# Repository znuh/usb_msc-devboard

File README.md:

# Devboard for USB mass storage

EDA: [KiCad7](https://www.kicad.org/)

## Parts
* MCU: [STM32F730R8Tx](https://www.st.com/en/microcontrollers-microprocessors/stm32f730r8.html) (or compatible)
* Mass storage: MicroSD via [DM3D-SF](https://www.hirose.com/product/series/DM3#) socket (attached to SDMMC1 of STM32)
* [USB3318](https://www.microchip.com/en-us/product/USB3318) USB high speed PHY
* 3.3V voltage regulator: [AP7313-33SR](https://www.diodes.com/part/view/AP7313/) or compatible
* PCB: 4 layer (Sig1, GND, 3.3V, Sig2) stackup
* 1x USB-C, 1x Micro USB
* 3x 0603 LEDs (power, user1, user2)
* 1x Button (Bootloader + user defined)
* passives: 0402 and 0603
* all componentes are on top, none on bottom

## Notes
* USB-C connector for hi-speed USB
* Micro USB connector for dev/debugging/DFU bootloader
* Testpads on bottom for UART (debugging, etc.)
* only one 13MHz crystal, connected to STM32 - MCO1 output of STM32 clocks USB PHY
* serial termination resistors in all clock lines

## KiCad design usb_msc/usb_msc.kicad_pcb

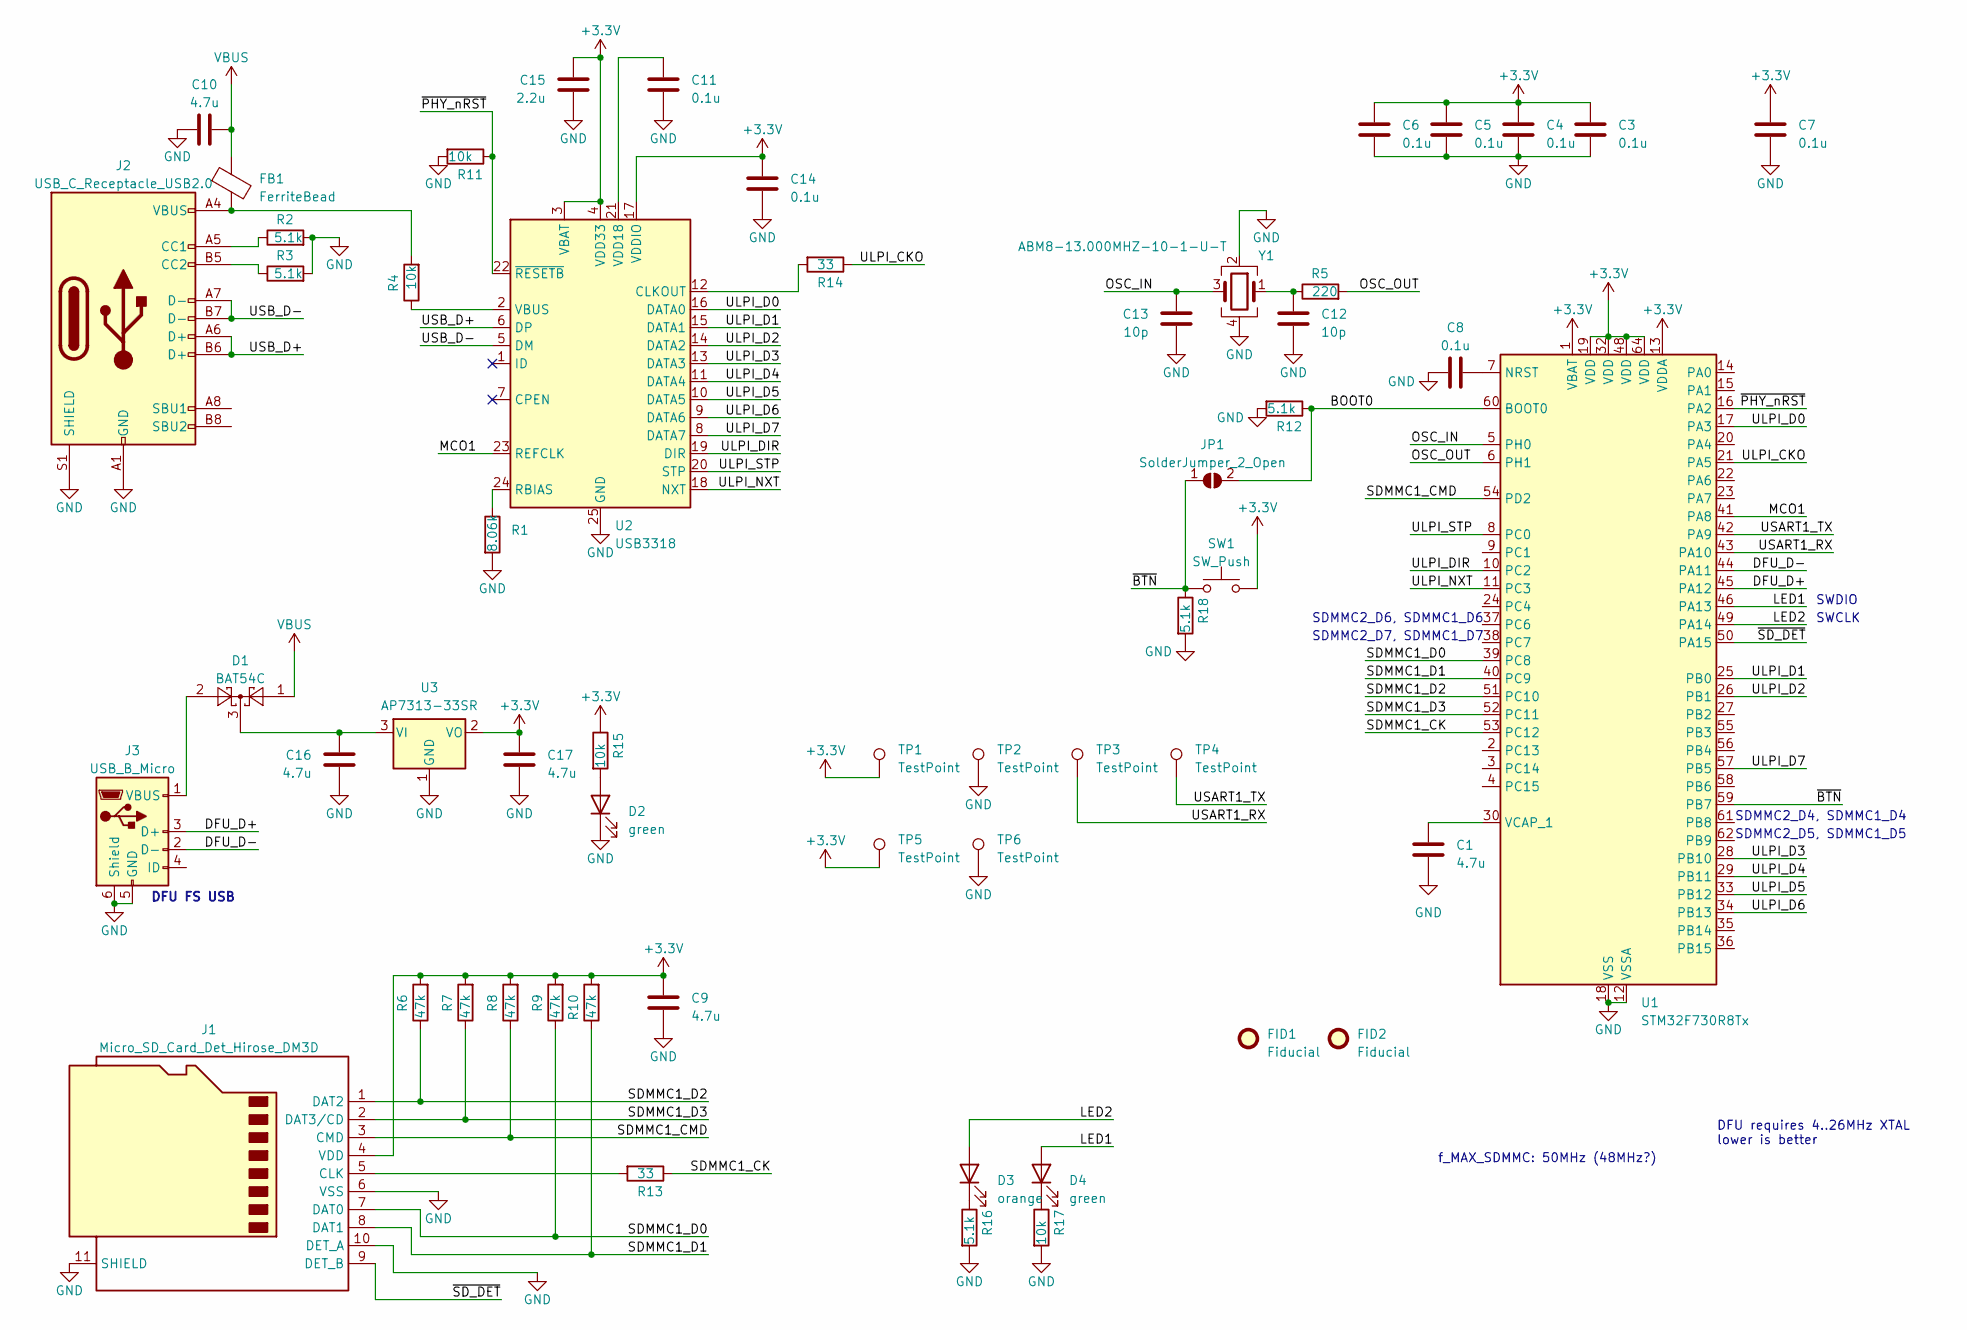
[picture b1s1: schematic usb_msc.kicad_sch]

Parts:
C1: 4.7u; C_0402_1005Metric
C3, C4, C5, C6, C7, C8, C11, C14: 0.1u; C_0402_1005Metric
C9, C10, C16, C17: 4.7u; C_0603_1608Metric
C12, C13: 10p; C_0402_1005Metric
C15: 2.2u; C_0402_1005Metric
D1: BAT54C; SOT-23
D2, D4: green; LED_0603_1608Metric
D3: orange; LED_0603_1608Metric
FB1: FerriteBead; L_0603_1608Metric
FID1, FID2: Fiducial; Fiducial_0.5mm_Mask1.5mm
J1: Micro_SD_Card_Det_Hirose_DM3D; microSD_HC_Hirose_DM3D-SF
J2: USB_C_Receptacle_USB2.0; USB_C_Receptacle_XKB_U262-16XN-4BVC11
J3: USB_B_Micro; USB_Micro-B_Amphenol_10103594-0001LF_Horizontal
JP1: SolderJumper_2_Open; SolderJumper-2_P1.3mm_Open_RoundedPad1.0x1.5mm
R1: 8.06k; R_0402_1005Metric
R2, R3, R12, R16, R18: 5.1k; R_0402_1005Metric
R4, R11, R15, R17: 10k; R_0402_1005Metric
R5: 220; R_0402_1005Metric
R6, R7, R8, R9, R10: 47k; R_0402_1005Metric
R13, R14: 33; R_0402_1005Metric
SW1: SW_Push; SMD_BTN
TP1, TP2, TP3, TP4, TP5, TP6: TestPoint; TestPoint_Pad_D1.0mm
U1: STM32F730R8Tx; LQFP-64_10x10mm_P0.5mm
U2: USB3318; QFN-24-1EP_4x4mm_P0.5mm_EP2.6x2.6mm_ThermalVias
U3: AP7313-33SR; SOT-23
Y1: ABM8-13.000MHZ-10-1-U-T; Crystal_SMD_Abracon_ABM8G-4Pin_3.2x2.5mm

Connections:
+3.3V: C3.2, C4.2, C5.2, C6.2, C7.2, C9.2, C14.2, C15.2, C17.1, J1.4 (VDD), R6.2, R7.2, R8.2, R9.2, R10.2, R15.1, SW1.2, TP1.1, TP5.1, U1.1 (VBAT), U1.13 (VDDA), U1.19 (VDD), U1.32 (VDD), U1.48 (VDD), U1.64 (VDD), U2.3 (VBAT), U2.4 (VDD33), U2.17 (VDDIO), U3.2 (VO)
/BOOT0: JP1.2 (B), R12.1, U1.60 (BOOT0)
/DFU_D+: J3.3 (D+), U1.45 (PA12)
/DFU_D-: J3.2 (D-), U1.44 (PA11)
/LED1: D4.2 (A), U1.46 (PA13)
/LED2: D3.2 (A), U1.49 (PA14)
/MCO1: U1.41 (PA8), U2.23 (REFCLK)
/OSC_IN: C13.2, U1.5 (PH0), Y1.3
/OSC_OUT: R5.2, U1.6 (PH1)
/SDMMC1_CK: R13.1, U1.53 (PC12)
/SDMMC1_CMD: J1.3 (CMD), R8.1, U1.54 (PD2)
/SDMMC1_D0: J1.7 (DAT0), R9.1, U1.39 (PC8)
/SDMMC1_D1: J1.8 (DAT1), R10.1, U1.40 (PC9)
/SDMMC1_D2: J1.1 (DAT2), R6.1, U1.51 (PC10)
/SDMMC1_D3: J1.2 (DAT3/CD), R7.1, U1.52 (PC11)
/ULPI_CKO: R14.1, U1.21 (PA5)
/ULPI_D0: U1.17 (PA3), U2.16 (DATA0)
/ULPI_D1: U1.25 (PB0), U2.15 (DATA1)
/ULPI_D2: U1.26 (PB1), U2.14 (DATA2)
/ULPI_D3: U1.28 (PB10), U2.13 (DATA3)
/ULPI_D4: U1.29 (PB11), U2.11 (DATA4)
/ULPI_D5: U1.33 (PB12), U2.10 (DATA5)
/ULPI_D6: U1.34 (PB13), U2.9 (DATA6)
/ULPI_D7: U1.57 (PB5), U2.8 (DATA7)
/ULPI_DIR: U1.10 (PC2), U2.19 (DIR)
/ULPI_NXT: U1.11 (PC3), U2.18 (NXT)
/ULPI_STP: U1.8 (PC0), U2.20 (STP)
/USART1_RX: TP3.1, U1.43 (PA10)
/USART1_TX: TP4.1, U1.42 (PA9)
/USB_D+: J2.A6 (D+), J2.B6 (D+), U2.6 (DP)
/USB_D-: J2.A7 (D-), J2.B7 (D-), U2.5 (DM)
/~BTN: JP1.1 (A), R18.1, SW1.1, U1.59 (PB7)
/~PHY_nRST: R11.1, U1.16 (PA2), U2.22 (~RESETB)
/~SD_DET: J1.9 (DET_B), U1.50 (PA15)
GND: C1.1, C3.1, C4.1, C5.1, C6.1, C7.1, C8.2, C9.1, C10.2, C11.1, C12.1, C13.1, C14.1, C15.1, C16.2, C17.2, D2.1 (K), J1.6 (VSS), J1.10 (DET_A), J1.11 (SHIELD), J2.A1 (GND), J2.A12 (GND), J2.B1 (GND), J2.B12 (GND), J2.S1 (SHIELD), J3.5 (GND), J3.6 (Shield), R1.2, R2.2, R3.2, R11.2, R12.2, R16.2, R17.2, R18.2, TP2.1, TP6.1, U1.12 (VSSA), U1.18 (VSS), U1.31 (VSS), U1.47 (VSS), U1.63 (VSS), U2.25 (GND), U3.1 (GND), Y1.2, Y1.4
unnamed: C12.2, R5.1, Y1.1
unnamed: D2.2 (A), R15.2
unnamed: D3.1 (K), R16.1
unnamed: D4.1 (K), R17.1
unnamed: FB1.2, J2.A4 (VBUS), J2.A9 (VBUS), J2.B4 (VBUS), J2.B9 (VBUS), R4.2
unnamed: J1.5 (CLK), R13.2
unnamed: J2.A5 (CC1), R2.1
unnamed: J2.B5 (CC2), R3.1
unnamed: D1.2, J3.1 (VBUS)
unnamed: C8.1, U1.7 (NRST)
unnamed: C1.2, U1.30 (VCAP_1)
unnamed: R14.2, U2.12 (CLKOUT)
unnamed: R1.1, U2.24 (RBIAS)
unnamed: R4.1, U2.2 (VBUS)
unnamed: C11.2, U2.21 (VDD18)
unnamed: C16.1, D1.3, U3.3 (VI)
VBUS: C10.1, D1.1, FB1.1

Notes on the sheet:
SWDIO
SDMMC2_D6, SDMMC1_D6
SDMMC2_D4, SDMMC1_D4
SWCLK
SDMMC2_D5, SDMMC1_D5
DFU FS USB
DFU requires 4..26MHz XTAL lower is better
f_MAX_SDMMC: 50MHz (48MHz?)
SDMMC2_D7, SDMMC1_D7

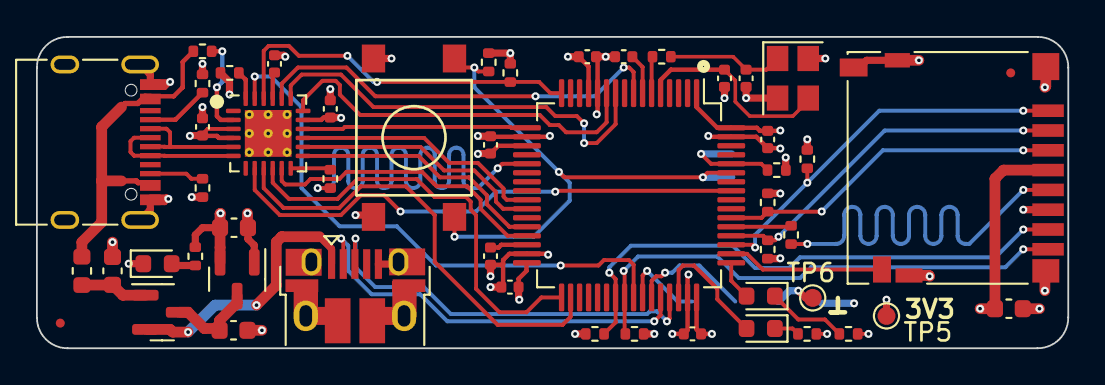
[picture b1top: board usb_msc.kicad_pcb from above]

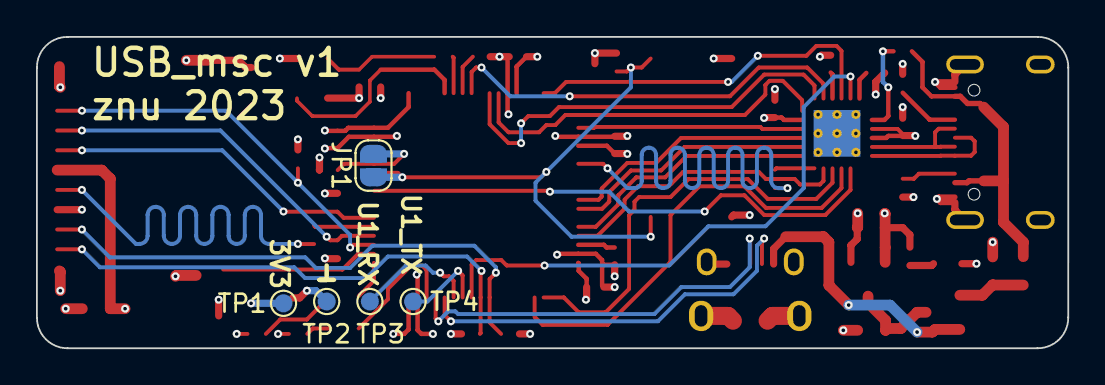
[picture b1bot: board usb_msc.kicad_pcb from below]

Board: 4 copper layers, 57.3 x 17.3 mm, 56 parts (5 on the bottom side), 52 nets.

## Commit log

2023-03-19 add license
2023-03-19 add kicad files
2023-03-19 add schematics as pdf
